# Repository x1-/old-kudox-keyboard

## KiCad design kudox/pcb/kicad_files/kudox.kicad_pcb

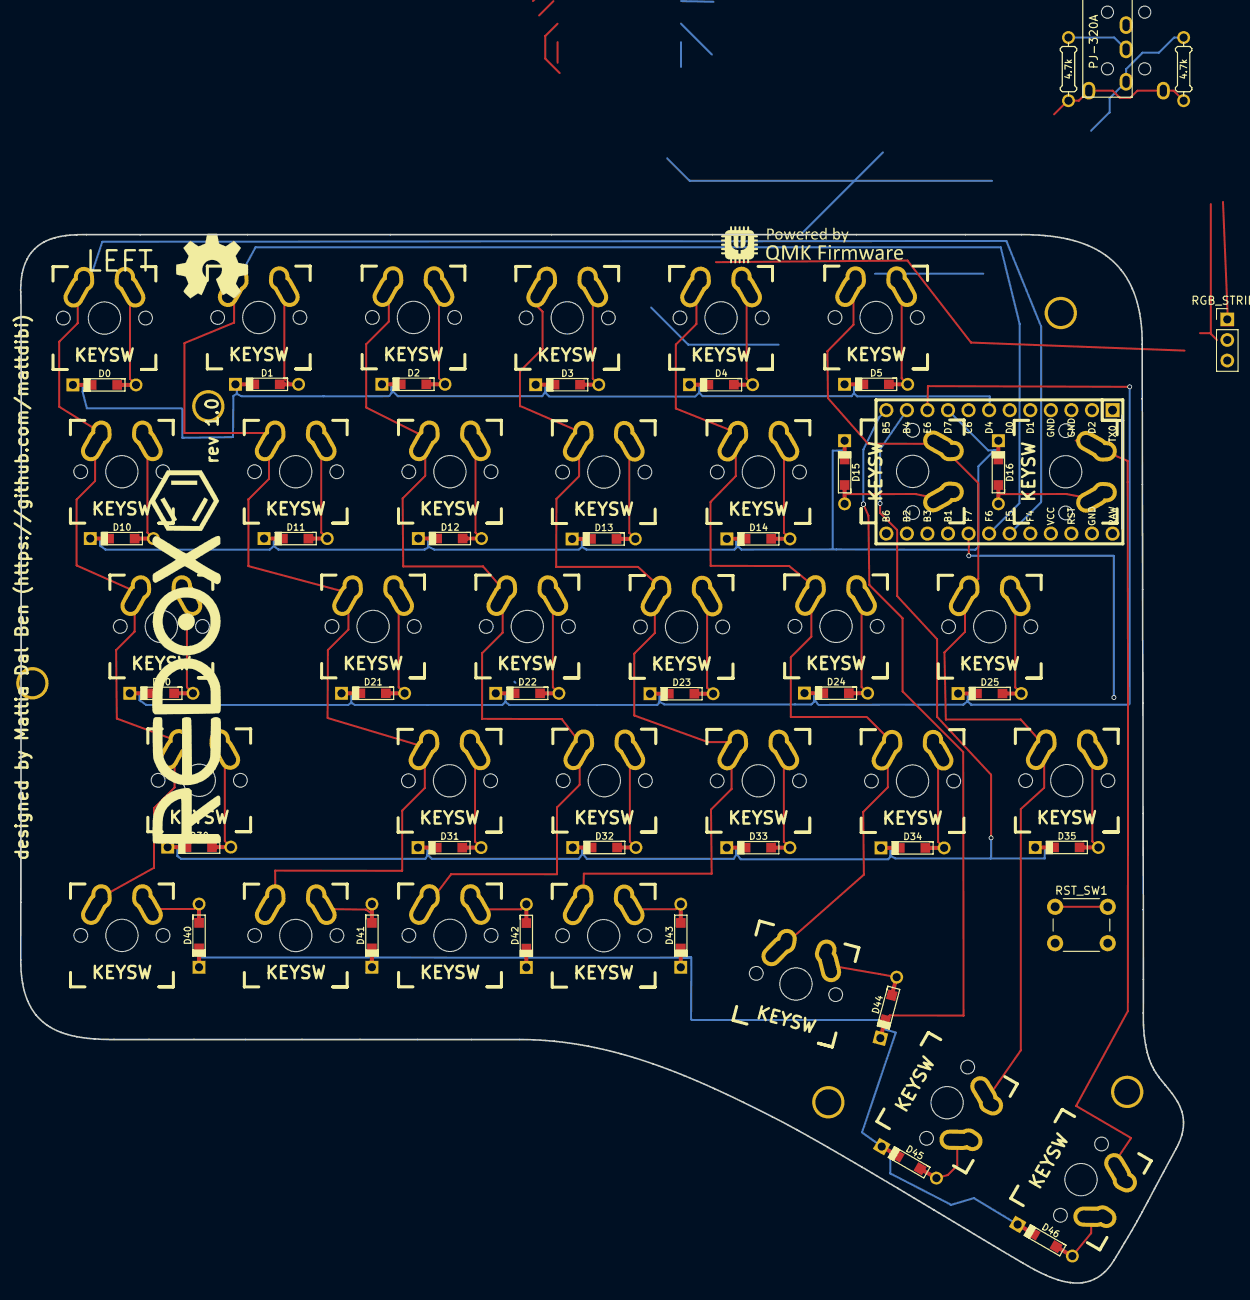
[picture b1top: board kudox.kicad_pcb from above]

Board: 2 copper layers, 143.6 x 129.5 mm, 75 parts (0 on the bottom side), 50 nets.

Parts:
D0, D1, D2, D3, D4, D5, D10, D11, D12, D13, D14, D15, D16, D20, D21, D22, D23, D24, D25, D30, D31, D32, D33, D34, D35, D40, D41, D42, D43, D44, D45, D46: D; Diode-dual
HOLE_M3, HOLE_M3#2, HOLE_M3#3, HOLE_M3#4, HOLE_M3#5: VAL**; HOLE_M3
K0, K10, K20, K30, K44: KEYSW; Mx_Alps_125-dualside
K1, K2, K3, K4, K5, K11, K12, K13, K14, K15, K21, K22, K23, K24, K25, K31, K32, K33, K34, K35, K40, K41, K42, K43: KEYSW; Mx_Alps_100-dualside
K16, K45, K46: KEYSW; Mx_Alps_150-dualsided
R1, R2: 4.7k; Resistor-Compact
RGB_STRIP1: Conn_01x03; Pin_Header_Straight_1x03_Pitch2.54mm
RST_SW1: SW_PUSH; SW_PUSH_6mm_h4.3mm
TRRS1: Audio-Jack-4; TRRS-PJ-320A-dual
U1: ProMicro; ArduinoProMicro

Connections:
GND: RGB_STRIP1.3, RST_SW1.2, TRRS1.4, U1.3, U1.4, U1.23
unnamed: D0.2, K0.2
unnamed: D1.2, K1.2
unnamed: D2.2, K2.2
unnamed: D3.2, K3.2
unnamed: D4.2, K4.2
unnamed: D5.2, K5.2
unnamed: D10.2, K10.2
unnamed: D11.2, K11.2
unnamed: D12.2, K12.2
unnamed: D13.2, K13.2
unnamed: D14.2, K14.2
unnamed: D15.2, K15.2
unnamed: D16.2, K16.2
unnamed: D20.2, K20.2
unnamed: D21.2, K21.2
unnamed: D22.2, K22.2
unnamed: D23.2, K23.2
unnamed: D24.2, K24.2
unnamed: D25.2, K25.2
unnamed: D30.2, K30.2
unnamed: D31.2, K31.2
unnamed: D32.2, K32.2
unnamed: D33.2, K33.2
unnamed: D34.2, K34.2
unnamed: D35.2, K35.2
unnamed: D40.2, K40.2
unnamed: D41.2, K41.2
unnamed: D42.2, K42.2
unnamed: D43.2, K43.2
unnamed: D44.2, K44.2
unnamed: D45.2, K45.2
unnamed: D46.2, K46.2
RST: RST_SW1.1, U1.22
SCL: R2.1, TRRS1.2, U1.6
SDA: R1.1, TRRS1.3, U1.5
VCC: R1.2, R2.2, RGB_STRIP1.1, TRRS1.1, U1.21
col0: K0.1, K10.1, K20.1, K30.1, K40.1, U1.19
col1: K1.1, K11.1, K21.1, K31.1, K41.1, U1.18
col2: K2.1, K12.1, K22.1, K32.1, K42.1, U1.17
col3: K3.1, K13.1, K23.1, K33.1, K43.1, U1.16
col4: K4.1, K14.1, K24.1, K34.1, K44.1, U1.15
col5: K5.1, K15.1, K25.1, K35.1, K45.1, U1.14
col6: K16.1, K46.1, U1.13
rgb_data: RGB_STRIP1.2, U1.1
row0: D0.1, D1.1, D2.1, D3.1, D4.1, D5.1, U1.7
row1: D10.1, D11.1, D12.1, D13.1, D14.1, D15.1, D16.1, U1.9
row2: D20.1, D21.1, D22.1, D23.1, D24.1, D25.1, U1.10
row3: D30.1, D31.1, D32.1, D33.1, D34.1, D35.1, U1.11
row4: D40.1, D41.1, D42.1, D43.1, D44.1, D45.1, D46.1, U1.12

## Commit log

2019-06-10 First commit!
2019-06-30 Modified pcb.
2019-06-30 Remove firmware/*.hex
